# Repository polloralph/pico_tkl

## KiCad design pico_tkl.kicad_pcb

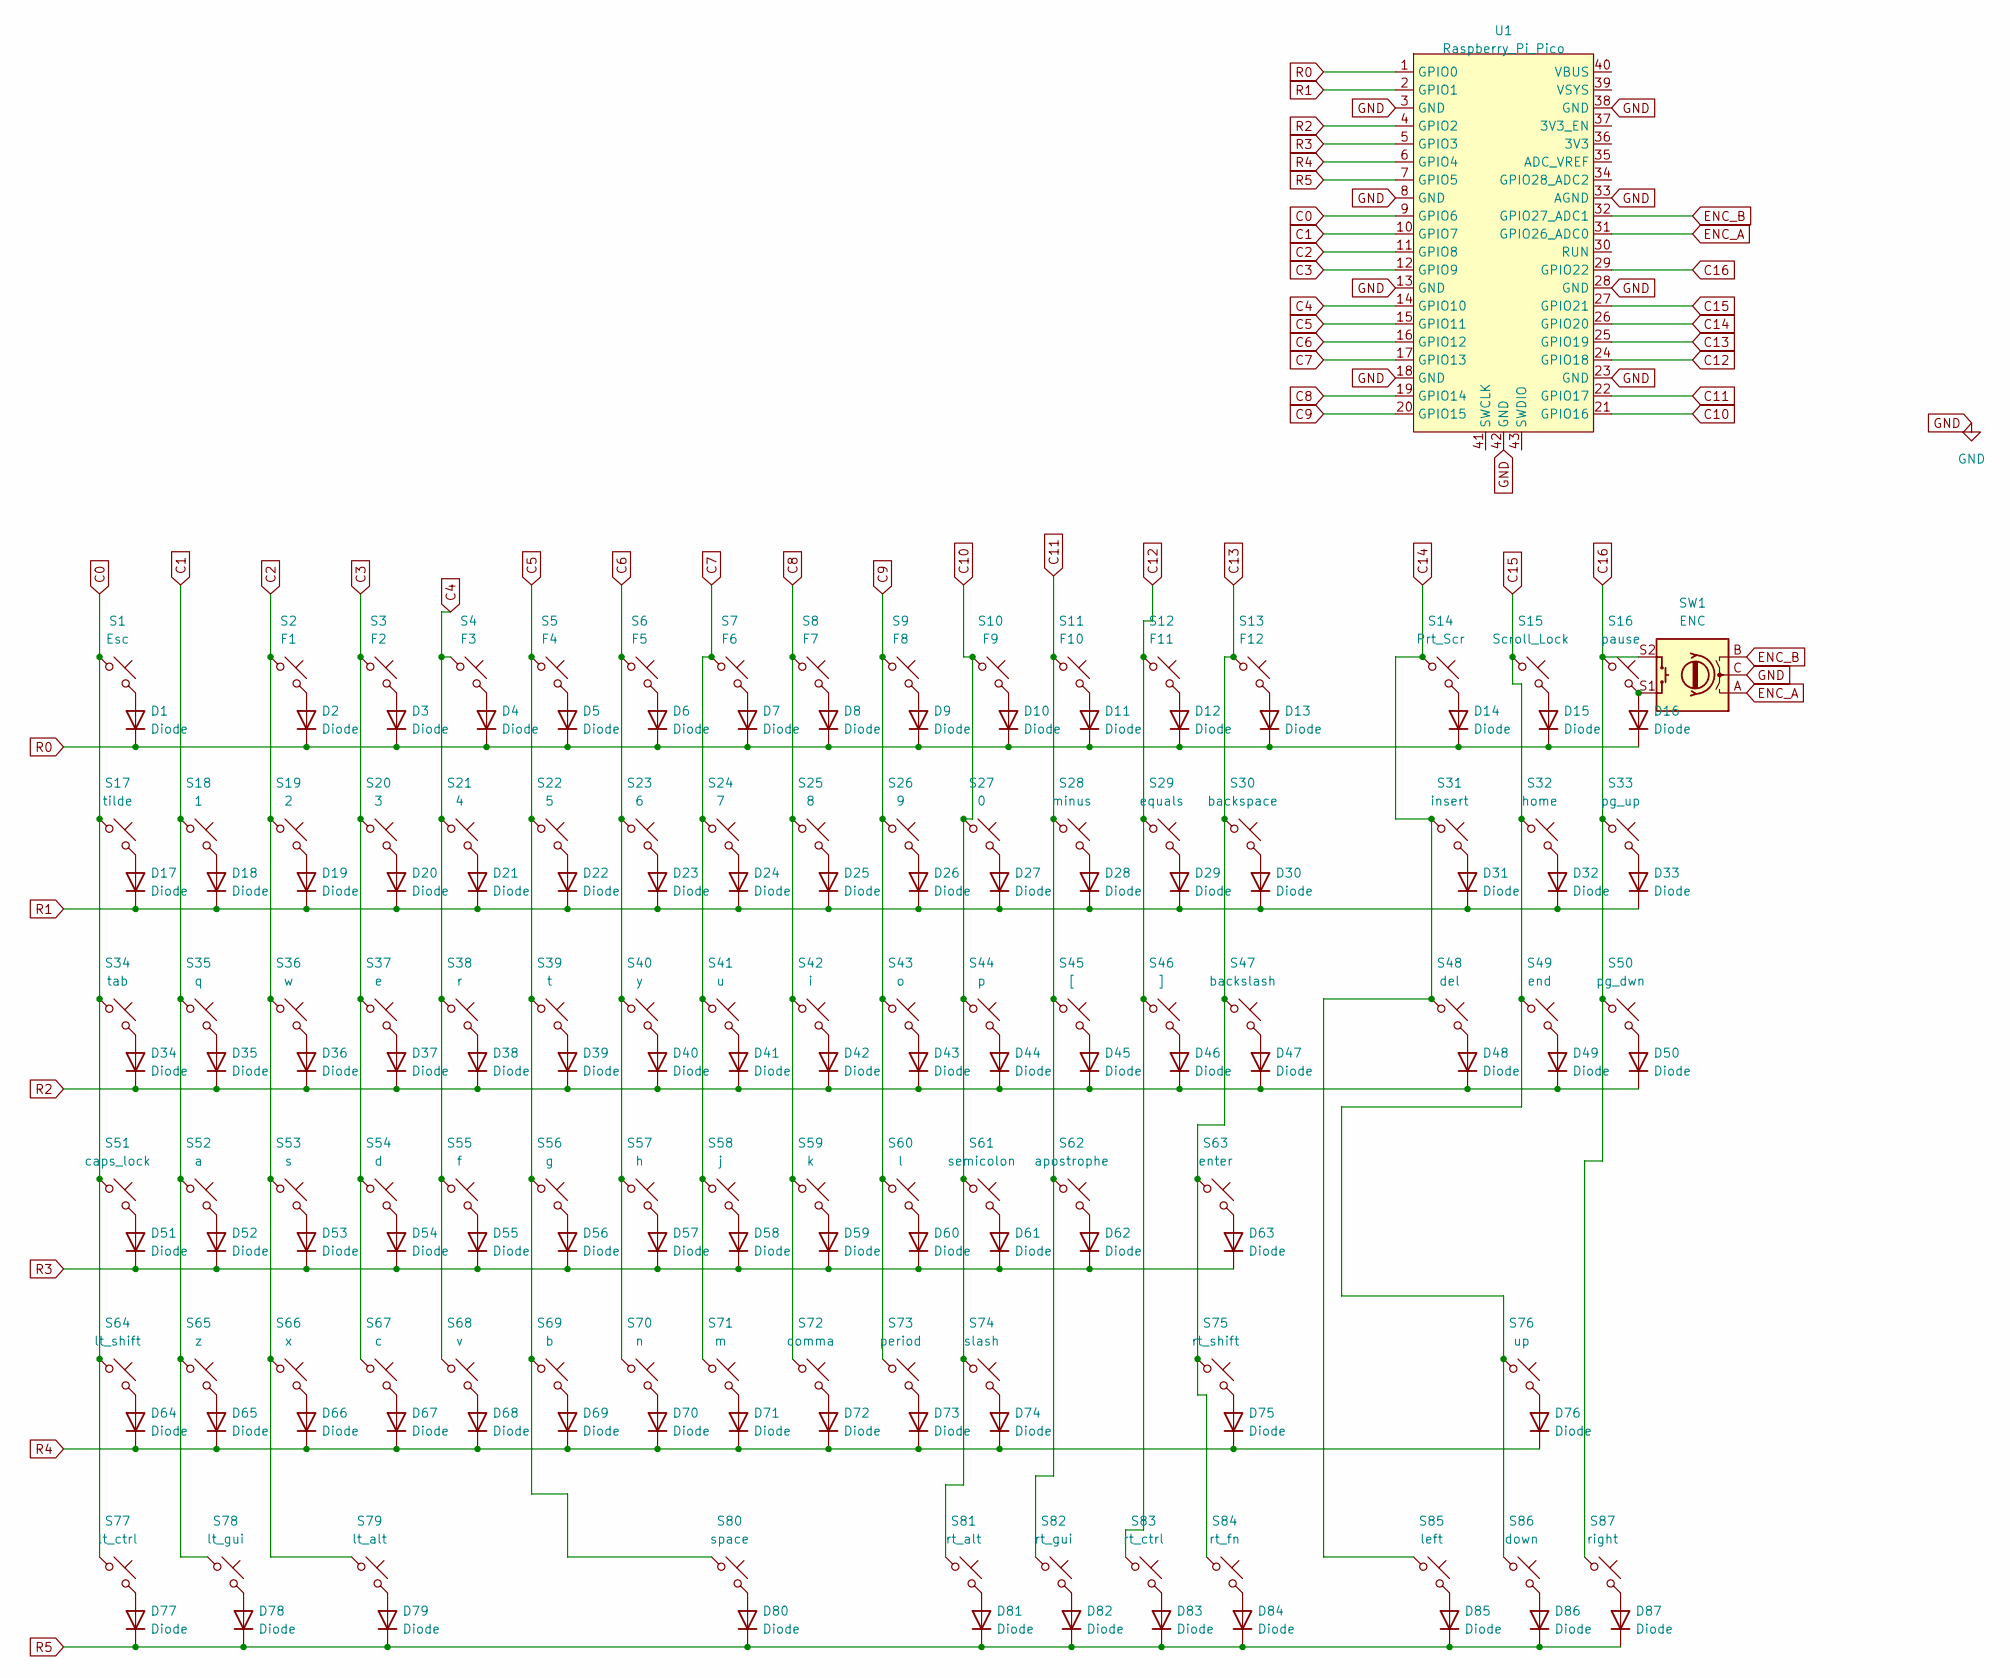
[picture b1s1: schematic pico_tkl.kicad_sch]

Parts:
D1, D2, D3, D4, D5, D6, D7, D8, D9, D10, D11, D12, D13, D14, D15, D16, D17, D18, D19, D20, D21, D22, D23, D24, D25, D26, D27, D28, D29, D30, D31, D32, D33, D34, D35, D36, D37, D38, D39, D40, D41, D42, D43, D44, D45, D46, D47, D48, D49, D50, D51, D52, D53, D54, D55, D56, D57, D58, D59, D60, D61, D62, D63, D64, D65, D66, D67, D68, D69, D70, D71, D72, D73, D74, D75, D76, D77, D78, D79, D80, D81, D82, D83, D84, D85, D86, D87: Diode; Diode-hybrid-3pad
S1: Esc; MX_PCB
S2: F1; MX_PCB
S3: F2; MX_PCB
S4: F3; MX_PCB
S5: F4; MX_PCB
S6: F5; MX_PCB
S7: F6; MX_PCB
S8: F7; MX_PCB
S9: F8; MX_PCB
S10: F9; MX_PCB
S11: F10; MX_PCB
S12: F11; MX_PCB
S13: F12; MX_PCB
S14: Prt_Scr; MX_PCB
S15: Scroll_Lock; MX_PCB
S16: pause; MX_PCB
S17: tilde; MX_PCB
S18: 1; MX_PCB
S19: 2; MX_PCB
S20: 3; MX_PCB
S21: 4; MX_PCB
S22: 5; MX_PCB
S23: 6; MX_PCB
S24: 7; MX_PCB
S25: 8; MX_PCB
S26: 9; MX_PCB
S27: 0; MX_PCB
S28: minus; MX_PCB
S29: equals; MX_PCB
S30: backspace; MX_PCB
S31: insert; MX_PCB
S32: home; MX_PCB
S33: pg_up; MX_PCB
S34: tab; MX_PCB
S35: q; MX_PCB
S36: w; MX_PCB
S37: e; MX_PCB
S38: r; MX_PCB
S39: t; MX_PCB
S40: y; MX_PCB
S41: u; MX_PCB
S42: i; MX_PCB
S43: o; MX_PCB
S44: p; MX_PCB
S45: [; MX_PCB
S46: ]; MX_PCB
S47: backslash; MX_PCB
S48: del; MX_PCB
S49: end; MX_PCB
S50: pg_dwn; MX_PCB
S51: caps_lock; MX_PCB
S52: a; MX_PCB
S53: s; MX_PCB
S54: d; MX_PCB
S55: f; MX_PCB
S56: g; MX_PCB
S57: h; MX_PCB
S58: j; MX_PCB
S59: k; MX_PCB
S60: l; MX_PCB
S61: semicolon; MX_PCB
S62: apostrophe; MX_PCB
S63: enter; MX_PCB
S64: lt_shift; MX_PCB
S65: z; MX_PCB
S66: x; MX_PCB
S67: c; MX_PCB
S68: v; MX_PCB
S69: b; MX_PCB
S70: n; MX_PCB
S71: m; MX_PCB
S72: comma; MX_PCB
S73: period; MX_PCB
S74: slash; MX_PCB
S75: rt_shift; MX_PCB
S76: up; MX_PCB
S77: lt_ctrl; MX_PCB
S78: lt_gui; MX_PCB
S79: lt_alt; MX_PCB
S80: space; MX_PCB
S81: rt_alt; MX_PCB
S82: rt_gui; MX_PCB
S83: rt_ctrl; MX_PCB
S84: rt_fn; MX_PCB
S85: left; MX_PCB
S86: down; MX_PCB
S87: right; MX_PCB
SW1: ENC; RotaryEncoder_EC11_Nonplated
U1: Raspberry_Pi_Pico; Raspberry_Pi_Pico_Flipped

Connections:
C0: S1.1, S17.1, S34.1, S51.1, S64.1, S77.1, U1.9 (GPIO6)
C1: S18.1, S35.1, S52.1, S65.1, S78.1, U1.10 (GPIO7)
C2: S2.1, S19.1, S36.1, S53.1, S66.1, S79.1, U1.11 (GPIO8)
C3: S3.1, S20.1, S37.1, S54.1, S67.1, U1.12 (GPIO9)
C4: S4.1, S21.1, S38.1, S55.1, S68.1, U1.14 (GPIO10)
C5: S5.1, S22.1, S39.1, S56.1, S69.1, S80.1, U1.15 (GPIO11)
C6: S6.1, S23.1, S40.1, S57.1, S70.1, U1.16 (GPIO12)
C7: S7.1, S24.1, S41.1, S58.1, S71.1, U1.17 (GPIO13)
C8: S8.1, S25.1, S42.1, S59.1, S72.1, U1.19 (GPIO14)
C9: S9.1, S26.1, S43.1, S60.1, S73.1, U1.20 (GPIO15)
C10: S10.1, S27.1, S44.1, S61.1, S74.1, S81.1, U1.21 (GPIO16)
C11: S11.1, S28.1, S45.1, S62.1, S82.1, U1.22 (GPIO17)
C12: S12.1, S29.1, S46.1, S83.1, U1.24 (GPIO18)
C13: S13.1, S30.1, S47.1, S63.1, S75.1, S84.1, U1.25 (GPIO19)
C14: S14.1, S31.1, S48.1, S85.1, U1.26 (GPIO20)
C15: S15.1, S32.1, S49.1, S76.1, S86.1, U1.27 (GPIO21)
C16: S16.1, S33.1, S50.1, S87.1, SW1.S2, U1.29 (GPIO22)
ENC_A: SW1.A, U1.31 (GPIO26_ADC0)
ENC_B: SW1.B, U1.32 (GPIO27_ADC1)
GND: SW1.C, U1.3 (GND), U1.8 (GND), U1.13 (GND), U1.18 (GND), U1.23 (GND), U1.28 (GND), U1.33 (AGND), U1.38 (GND), U1.42 (GND)
unnamed: D1.2 (A), S1.2
unnamed: D2.2 (A), S2.2
unnamed: D3.2 (A), S3.2
unnamed: D4.2 (A), S4.2
unnamed: D5.2 (A), S5.2
unnamed: D6.2 (A), S6.2
unnamed: D7.2 (A), S7.2
unnamed: D8.2 (A), S8.2
unnamed: D9.2 (A), S9.2
unnamed: D10.2 (A), S10.2
unnamed: D11.2 (A), S11.2
unnamed: D12.2 (A), S12.2
unnamed: D13.2 (A), S13.2
unnamed: D14.2 (A), S14.2
unnamed: D15.2 (A), S15.2
unnamed: D16.2 (A), S16.2, SW1.S1
unnamed: D17.2 (A), S17.2
unnamed: D18.2 (A), S18.2
unnamed: D19.2 (A), S19.2
unnamed: D20.2 (A), S20.2
unnamed: D21.2 (A), S21.2
unnamed: D22.2 (A), S22.2
unnamed: D23.2 (A), S23.2
unnamed: D24.2 (A), S24.2
unnamed: D25.2 (A), S25.2
unnamed: D26.2 (A), S26.2
unnamed: D27.2 (A), S27.2
unnamed: D28.2 (A), S28.2
unnamed: D29.2 (A), S29.2
unnamed: D30.2 (A), S30.2
unnamed: D31.2 (A), S31.2
unnamed: D32.2 (A), S32.2
unnamed: D33.2 (A), S33.2
unnamed: D34.2 (A), S34.2
unnamed: D35.2 (A), S35.2
unnamed: D36.2 (A), S36.2
unnamed: D37.2 (A), S37.2
unnamed: D38.2 (A), S38.2
unnamed: D39.2 (A), S39.2
unnamed: D40.2 (A), S40.2
unnamed: D41.2 (A), S41.2
unnamed: D42.2 (A), S42.2
unnamed: D43.2 (A), S43.2
unnamed: D44.2 (A), S44.2
unnamed: D45.2 (A), S45.2
unnamed: D46.2 (A), S46.2
unnamed: D47.2 (A), S47.2
unnamed: D48.2 (A), S48.2
unnamed: D49.2 (A), S49.2
unnamed: D50.2 (A), S50.2
unnamed: D51.2 (A), S51.2
unnamed: D52.2 (A), S52.2
unnamed: D53.2 (A), S53.2
unnamed: D54.2 (A), S54.2
unnamed: D55.2 (A), S55.2
unnamed: D56.2 (A), S56.2
unnamed: D57.2 (A), S57.2
unnamed: D58.2 (A), S58.2
unnamed: D59.2 (A), S59.2
unnamed: D60.2 (A), S60.2
unnamed: D61.2 (A), S61.2
unnamed: D62.2 (A), S62.2
unnamed: D63.2 (A), S63.2
unnamed: D64.2 (A), S64.2
unnamed: D65.2 (A), S65.2
unnamed: D66.2 (A), S66.2
unnamed: D67.2 (A), S67.2
unnamed: D68.2 (A), S68.2
unnamed: D69.2 (A), S69.2
unnamed: D70.2 (A), S70.2
unnamed: D71.2 (A), S71.2
unnamed: D72.2 (A), S72.2
unnamed: D73.2 (A), S73.2
unnamed: D74.2 (A), S74.2
unnamed: D75.2 (A), S75.2
unnamed: D76.2 (A), S76.2
unnamed: D77.2 (A), S77.2
unnamed: D78.2 (A), S78.2
unnamed: D79.2 (A), S79.2
unnamed: D80.2 (A), S80.2
unnamed: D81.2 (A), S81.2
unnamed: D82.2 (A), S82.2
unnamed: D83.2 (A), S83.2
unnamed: D84.2 (A), S84.2
unnamed: D85.2 (A), S85.2
unnamed: D86.2 (A), S86.2
unnamed: D87.2 (A), S87.2
R0: D1.1 (K), D2.1 (K), D3.1 (K), D4.1 (K), D5.1 (K), D6.1 (K), D7.1 (K), D8.1 (K), D9.1 (K), D10.1 (K), D11.1 (K), D12.1 (K), D13.1 (K), D14.1 (K), D15.1 (K), D16.1 (K), U1.1 (GPIO0)
R1: D17.1 (K), D18.1 (K), D19.1 (K), D20.1 (K), D21.1 (K), D22.1 (K), D23.1 (K), D24.1 (K), D25.1 (K), D26.1 (K), D27.1 (K), D28.1 (K), D29.1 (K), D30.1 (K), D31.1 (K), D32.1 (K), D33.1 (K), U1.2 (GPIO1)
R2: D34.1 (K), D35.1 (K), D36.1 (K), D37.1 (K), D38.1 (K), D39.1 (K), D40.1 (K), D41.1 (K), D42.1 (K), D43.1 (K), D44.1 (K), D45.1 (K), D46.1 (K), D47.1 (K), D48.1 (K), D49.1 (K), D50.1 (K), U1.4 (GPIO2)
R3: D51.1 (K), D52.1 (K), D53.1 (K), D54.1 (K), D55.1 (K), D56.1 (K), D57.1 (K), D58.1 (K), D59.1 (K), D60.1 (K), D61.1 (K), D62.1 (K), D63.1 (K), U1.5 (GPIO3)
R4: D64.1 (K), D65.1 (K), D66.1 (K), D67.1 (K), D68.1 (K), D69.1 (K), D70.1 (K), D71.1 (K), D72.1 (K), D73.1 (K), D74.1 (K), D75.1 (K), D76.1 (K), U1.6 (GPIO4)
R5: D77.1 (K), D78.1 (K), D79.1 (K), D80.1 (K), D81.1 (K), D82.1 (K), D83.1 (K), D84.1 (K), D85.1 (K), D86.1 (K), D87.1 (K), U1.7 (GPIO5)

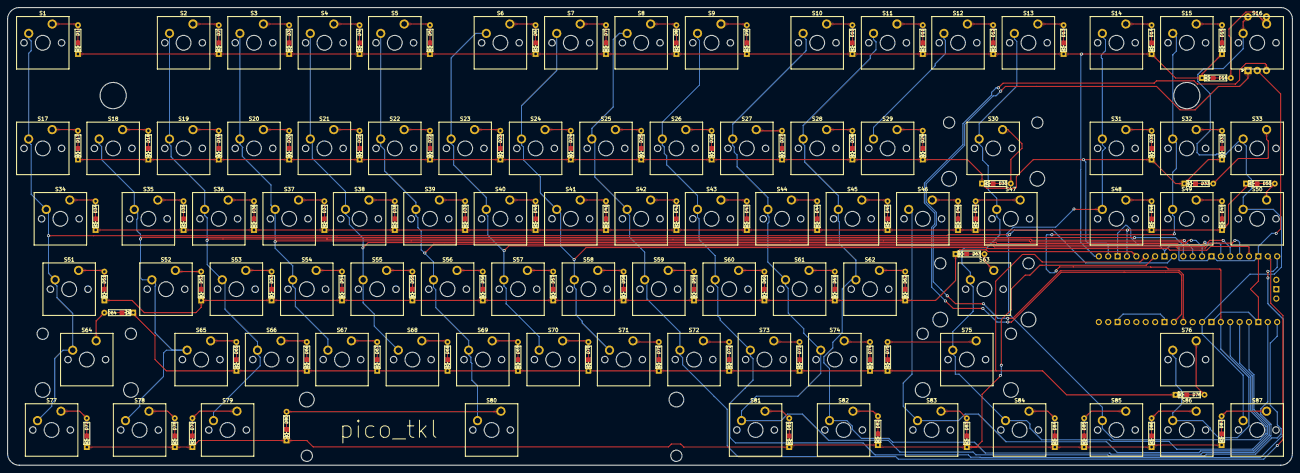
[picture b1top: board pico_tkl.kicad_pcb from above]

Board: 2 copper layers, 347.7 x 123.8 mm, 176 parts (0 on the bottom side), 113 nets.

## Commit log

2023-11-26 init kicad
2023-11-26 lib files added
2023-11-30 datasheet for switches.
